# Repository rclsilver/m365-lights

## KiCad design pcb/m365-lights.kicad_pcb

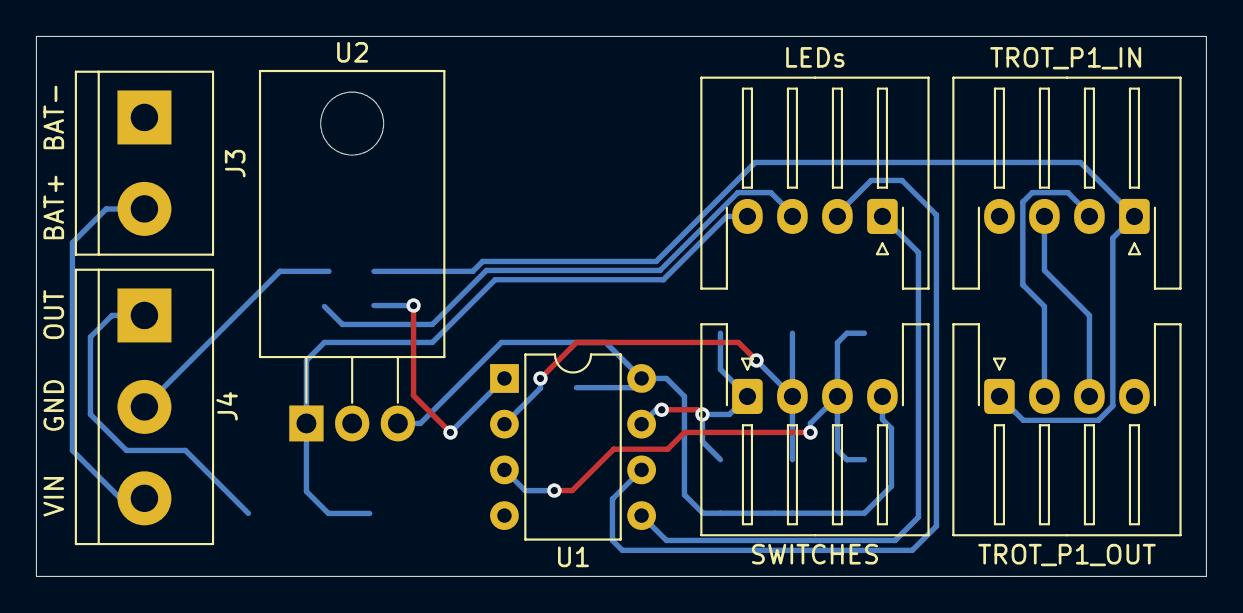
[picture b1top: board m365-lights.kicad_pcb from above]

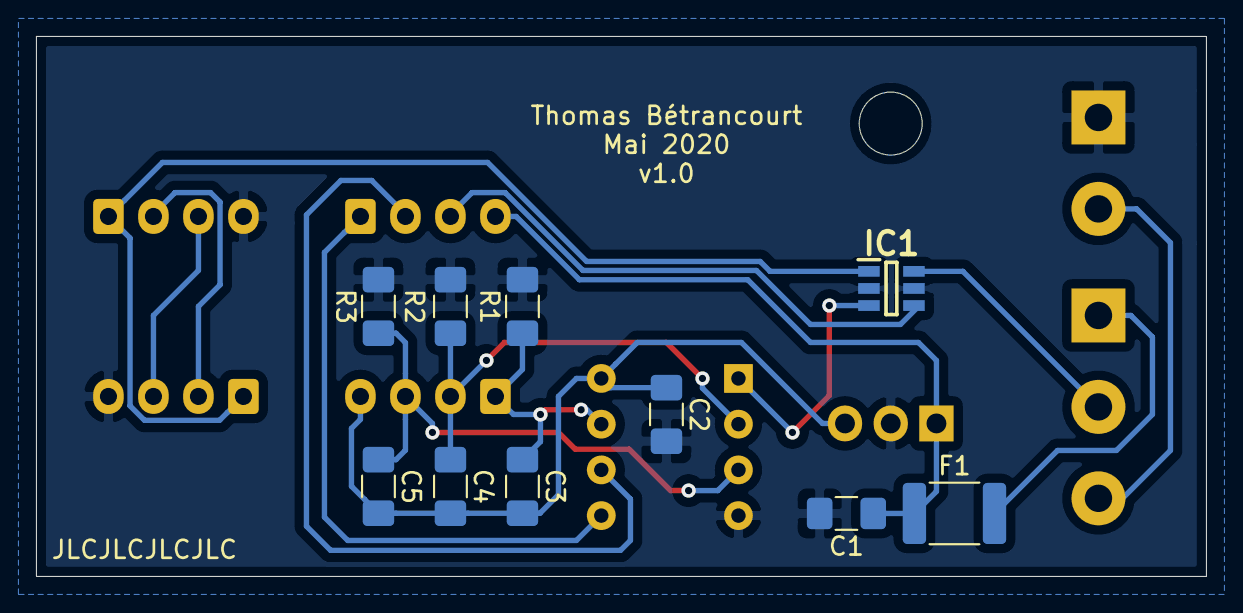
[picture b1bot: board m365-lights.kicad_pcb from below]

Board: 2 copper layers, 65.0 x 30.0 mm, 18 parts (10 on the bottom side), 16 nets.

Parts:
C1, C2, C3, C4, C5: 1uF; C_1206_3216Metric_Pad1.42x1.75mm_HandSolder
F1: Fuse; Fuse_1812_4532Metric_Pad1.30x3.40mm_HandSolder
IC1: NDC7002N
J3: BATTERY; TerminalBlock_bornier-2_P5.08mm
J4: BUCK; TerminalBlock_bornier-3_P5.08mm
LEDs: LEDs; JST_XH_S4B-XH-A-1_1x04_P2.50mm_Horizontal
R1, R2, R3: 10k; R_1206_3216Metric_Pad1.42x1.75mm_HandSolder
SWITCHES: SWITCHES; JST_XH_S4B-XH-A-1_1x04_P2.50mm_Horizontal
TROT_P1_IN: TROT_P1_IN; JST_XH_S4B-XH-A-1_1x04_P2.50mm_Horizontal
TROT_P1_OUT: TROT_P1_OUT; JST_XH_S4B-XH-A-1_1x04_P2.50mm_Horizontal
U1: ATtiny85-20PU; DIP-8_W7.62mm
U2: LM7805_TO220; TO-220-3_Horizontal_TabDown

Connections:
+5V: C2.1, C3.2, C4.2, C5.2, SWITCHES.4, U1.8, U2.3
+12V: C1.1, F1.1, LEDs.4, U2.1
+BATT: J3.2, J4.3
/LED_LEFT: LEDs.1, U1.5
/LED_RIGHT: LEDs.2, U1.6
/MOSFET_A_D: IC1.6, J4.2
/MOSFET_A_G: IC1.1, TROT_P1_IN.1, TROT_P1_OUT.1
/MOSFET_B_D: IC1.4, LEDs.3
/MOSFET_B_G: IC1.3, U1.1
/SW_LEFT: C3.1, R1.1, SWITCHES.1, U1.7
/SW_LIGHTS: C5.1, R3.1, SWITCHES.3, U1.3
/SW_RIGHT: C4.1, R2.2, SWITCHES.2, U1.2
GND: C1.2, C2.2, IC1.2, IC1.5, J3.1, R1.2, R2.1, R3.2, TROT_P1_IN.4, TROT_P1_OUT.4, U1.4, U2.2
unnamed: F1.2, J4.1
unnamed: TROT_P1_IN.2, TROT_P1_OUT.2
unnamed: TROT_P1_IN.3, TROT_P1_OUT.3

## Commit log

2020-05-11 Initial version
